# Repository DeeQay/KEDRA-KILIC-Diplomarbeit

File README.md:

<div align="center">

# LiDAR Mapping RC Vehicle

**Remote-controlled vehicle with real-time 360° LiDAR mapping and on-controller path planning**

Diploma thesis (Diplomarbeit) · HTL Donaustadt, Vienna · 2023/24
**David Kedra** and **Berdan Kilic**

</div>

## Overview

A four-wheel vehicle carries a 360° laser distance sensor (LiDAR) and streams its measurements over Bluetooth to a handheld controller. The controller turns the raw data into a live top-down map of the vehicle's surroundings, shows it on a 3.5" display and drives the vehicle via joystick. The user can pick any point on the map, and the controller computes and draws the shortest route around the obstacles to get there.

Both devices run on ESP32 microcontrollers. The firmware, the communication protocol and the controller PCB were designed from scratch.

<table>
  <tr>
    <td align="center"><br><sub>The real environment</sub></td>
    <td align="center"><br><sub>The same corner as seen on the controller</sub></td>
  </tr>
</table>

## The problem

A remote-controlled vehicle is only really usable while the operator can see it. Once it drives around a corner or into another room, the operator has no idea what is around it. That rules out exactly the use cases where such a vehicle would be most helpful, such as inspection, surveillance or exploring spaces a person cannot easily enter. A camera stream is the usual answer, but it needs a lot of bandwidth and only shows one direction.

**Goal of the thesis:** give the operator a full 360° picture of the vehicle's surroundings in real time, over a simple low-bandwidth wireless link, and help them find a route to a chosen point.

## The solution

| Challenge | Approach |
|---|---|
| See all directions at once | LD19 360° LiDAR on the vehicle, read over UART at 230 400 baud, every packet verified with CRC-8 |
| Send scan data over a slow wireless link | Own lightweight message protocol over Bluetooth Classic (SPP). Only *angle + distance* pairs are sent, paced by a hardware timer interrupt |
| Sensor noise | Plausibility filter on the controller that discards physically impossible jumps between consecutive measurements |
| Turn measurements into a map | Polar to Cartesian conversion into a 30 × 20 occupancy grid (free / obstacle / unknown), with ray-tracing to mark the free space between sensor and obstacle |
| Show it fast on a small display | Incremental rendering: only grid cells that changed since the last frame are redrawn on the 480 × 320 SPI display |
| Find a way to a target | Target selected with the joystick, shortest path computed with the **Lee algorithm** (breadth-first wavefront search, 8-neighbourhood) and drawn on the map |
| Drive the vehicle | Joystick values travel back over the same link and are mapped to PWM for four DC motors via two L298 H-bridges |

## System architecture

```mermaid
flowchart TB
    subgraph Vehicle["Vehicle · ESP32"]
        direction LR
        L[LD19 LiDAR<br/>360°, UART] --> P[Packet parser<br/>+ CRC-8]
        P --> T[Timer interrupt<br/>send scheduling]
        M[Motor control<br/>2× L298, 4 DC motors]
    end

    subgraph Controller["Controller · ESP32"]
        direction LR
        F[Noise filter] --> MAP[Occupancy grid<br/>30 × 20]
        MAP --> D[TFT display<br/>480 × 320, SPI]
        MAP --> LEE[Lee algorithm<br/>path planning]
        LEE --> D
        J[Joystick + button]
    end

    T -- "angle, distance" --> F
    J -- "x, y" --> M
```

Both arrows between the devices run over a single Bluetooth Classic connection (controller = master, vehicle = slave).

## Engineering decisions

**Choosing the platform.** The hardware went through three iterations before it worked reliably:

| Iteration | Setup | Why it was dropped |
|---|---|---|
| 1 | 2× Arduino Nano + HC-05 Bluetooth modules | Not enough memory and CPU for the map, display and LiDAR processing |
| 2 | Raspberry Pi 4 (controller) + ESP32 (vehicle) | No Linux driver library for the ILI9488 display. Writing one would have taken too long |
| 3 | 2× ESP32 with built-in Bluetooth | **Final.** Dropping the external modules also gave faster transfer, quicker pairing and lower latency |

**Optimising the mapping code.** The controller has to process LiDAR data, redraw the display and send joystick values at the same time, so the coordinate conversion was profiled on the ESP32. A benchmark of 720 rays took about 2200 ms. Caching sine and cosine per angle and pre-computing all constant scale factors brought it down to about 1500 ms, roughly **32 % faster**, see [`LidarMapper::calcPosition`](Programmcode/Fernsteuerung/LidarMapper.cpp).

**Low cost.** The main components (ESP32s, LiDAR, display, chassis with motors, motor drivers) cost about 130 €.

## Features

**Live 360° map** with the vehicle always in the centre. Five mapping modes, switched with the button:

| Mode | Behaviour |
|---|---|
| Save | Accumulates all measurements. Best while the vehicle stands still |
| Overwrite | New measurements replace old ones along the same ray. Best while driving |
| Full rotation | Redraws the map after each complete 360° sweep |
| Full rotation, slow | Same, with finer angular resolution |
| Automatic | Switches between *Save* and *Overwrite* depending on whether the joystick is idle |

**Route planning.** Press the joystick, move the cursor to a target, confirm. The shortest path around all known obstacles is calculated and shown:

<table>
  <tr>
    <td align="center"><br><sub>1. Select a target (blue)</sub></td>
    <td align="center"><br><sub>2. Shortest route around the wall (purple)</sub></td>
  </tr>
</table>

<details>
<summary><b>How the Lee algorithm works</b></summary>
<br>

Starting at the vehicle (`ST`), every reachable cell is labelled with its distance in steps, wave by wave, until the target (`EN`) is reached. Obstacles (`##`) are never entered. Walking back from the target along decreasing numbers gives the shortest path.

Implementation: [`LeeAlgorithm.cpp`](Programmcode/Fernsteuerung/LeeAlgorithm.cpp)
</details>

**More:**
- Adjustable range from 0.5 m to 12 m in 0.5 m steps (hold the joystick)
- Reset the map (hold the button)
- Automatic Bluetooth reconnect when the link drops

## Hardware

<table>
  <tr>
    <td align="center"><br><sub>Vehicle with LD19 LiDAR on top</sub></td>
    <td align="center"><br><sub>Controller on its own PCB</sub></td>
  </tr>
</table>

| | Vehicle | Controller |
|---|---|---|
| Microcontroller | ESP32 | ESP32 DevKit V1 |
| Input | LDROBOT LD19 360° LiDAR | Analog joystick (SparkFun COM-09032), push button |
| Output | 4 DC motors via 2× L298 H-bridge | 3.5" TFT, 480 × 320, ILI9488, SPI |
| Design files | [`Platinen/Fahrzeug`](Platinen/Fahrzeug) | [`Platinen/Fernsteuerung`](Platinen/Fernsteuerung) |

<details>
<summary><b>Controller schematic</b></summary>
<br>

</details>

## Bluetooth protocol

Each message is a short list of integers, sent as ASCII digits:

```
<type> \n <value 1> \n <value 2> \0
```

| Type | Direction | Values |
|---|---|---|
| `0` JOYSTICK | controller → vehicle | x, y (12-bit ADC) |
| `1` LIDAR | vehicle → controller | angle (°), distance (mm) |

The receiver checks length and characters and drops corrupted messages instead of acting on them.

## Repository structure

```
Programmcode/
├── Fahrzeug/           Vehicle firmware: LiDAR driver, motor control, Bluetooth slave
└── Fernsteuerung/      Controller firmware: mapping, display, Lee algorithm, joystick, Bluetooth master
Platinen/               EAGLE schematics (.sch) and board layouts (.brd)
docs/                   Presentation, project pitch, images
Lidar doku/             LD19 datasheet
Display doku/           Display manual, Adafruit GFX reference
Umgebungsspeicherung/   Early test code for the mapping logic
```

## Build and flash

1. Install the [Arduino IDE](https://www.arduino.cc/en/software) and the **esp32** board package by Espressif.
2. Install the controller libraries via the Library Manager: `Adafruit GFX Library`, `ILI9486_SPI`.
3. Upload `Programmcode/Fahrzeug/Fahrzeug.ino` to the vehicle ESP32.
4. Upload `Programmcode/Fernsteuerung/Fernsteuerung.ino` to the controller ESP32.
5. Power both. The controller finds and connects to the vehicle automatically.

> On the vehicle the LiDAR is read on the same hardware UART as the USB serial port, so its TX line may need to be disconnected while uploading.

## Team

| | Responsibilities |
|---|---|
| **David Kedra** ([@DeeQay](https://github.com/DeeQay)), project lead | Bluetooth communication and protocol, map visualisation, environment mapping, route planning. Controller hardware and PCB |
| **Berdan Kilic** ([@kilic7](https://github.com/kilic7)) | Vehicle control and motor drivers, 360° LiDAR data acquisition. Vehicle hardware and PCB |

Supervisors: Ahmet Kilic, Heinrich Haager

## Documents

- [**Diploma thesis** (PDF, German)](docs/Diplomarbeit.pdf)
- [Final presentation (PDF, German)](docs/Diplomarbeit_Praesentation.pdf)
- [Project pitch, October 2023 (PDF, German)](docs/Projektvorstellung_2023-10.pdf)
- [Project description (German)](Diplomarbeit%20Projektbeschreibung.docx)

## Limitations and next steps

- **No odometry.** The map is always relative to the vehicle's current position and is refreshed while driving, not stitched into one global map. Wheel encoders or an IMU would allow real SLAM.
- **Route is advisory.** The path is shown to the operator, the vehicle does not follow it on its own yet.
- **Bandwidth.** Bluetooth Classic limits how many points per second reach the controller, which is why the grid is kept coarse (30 × 20). BLE or Wi-Fi (ESP-NOW) would allow a finer map.

---

<sub>Code comments and project documents are in German.</sub>

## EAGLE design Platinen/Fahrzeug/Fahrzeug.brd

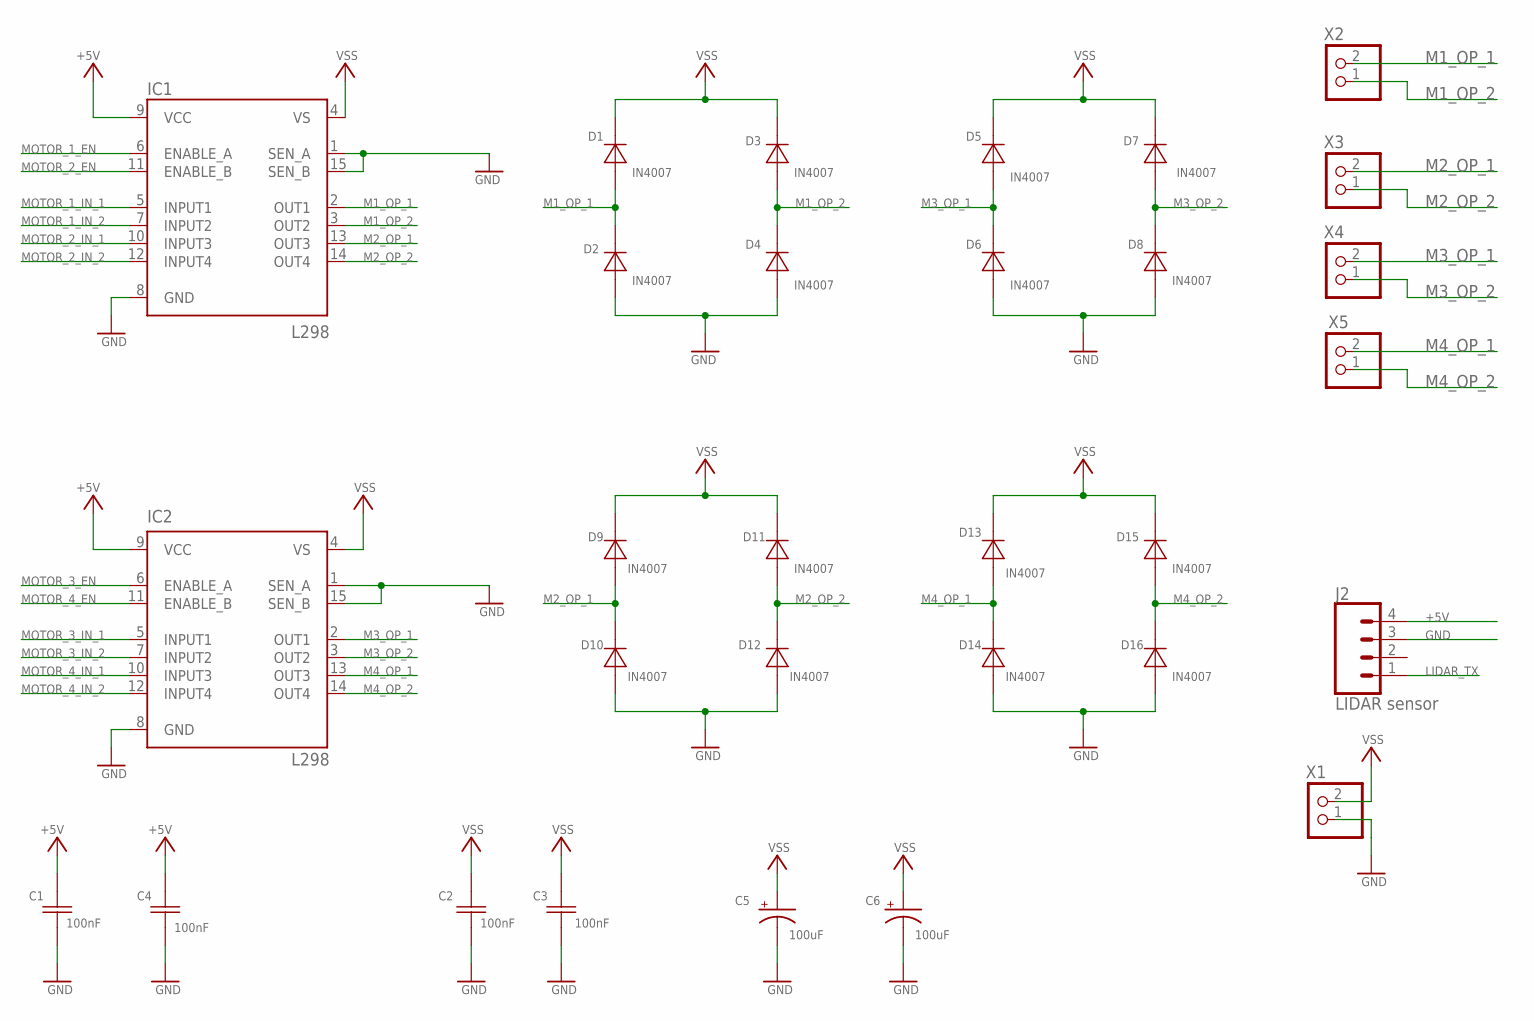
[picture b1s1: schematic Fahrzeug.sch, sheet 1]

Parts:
C1, C2, C3, C4: 100nF; R1206
C5, C6: 100uF; CPOL-RADIAL-2.5MM-6.5MM
D1, D2, D3, D4, D5, D6, D7, D8, D9, D10, D11, D12, D13, D14, D15, D16: IN4007; DO214AC
IC1, IC2: L298; MULTIWATT-15
J2: LIDAR sensor; MOLEX-1X4
X1, X2, X3, X4, X5: PINHD-1X2; 1X02

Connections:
+5V: C1.2, C4.2, IC1.9 (VCC), IC2.9 (VCC), J2.4; also elsewhere on the board
GND: C1.1, C2.1, C3.1, C4.1, C5.2 (-), C6.2 (-), D2.A, D4.A, D6.A, D8.A, D10.A, D12.A, D14.A, D16.A, IC1.1 (SEN_A), IC1.8 (GND), IC1.15 (SEN_B), IC2.1 (SEN_A), IC2.8 (GND), IC2.15 (SEN_B), J2.3, X1.1; also elsewhere on the board
LIDAR_TX: J2.1; also elsewhere on the board
M1_OP_1: D1.A, D2.C, IC1.2 (OUT1), X2.2
M1_OP_2: D3.A, D4.C, IC1.3 (OUT2), X2.1
M2_OP_1: D9.A, D10.C, IC1.13 (OUT3), X3.2
M2_OP_2: D11.A, D12.C, IC1.14 (OUT4), X3.1
M3_OP_1: D5.A, D6.C, IC2.2 (OUT1), X4.2
M3_OP_2: D7.A, D8.C, IC2.3 (OUT2), X4.1
M4_OP_1: D13.A, D14.C, IC2.13 (OUT3), X5.2
M4_OP_2: D15.A, D16.C, IC2.14 (OUT4), X5.1
MOTOR_1_EN: IC1.6 (ENABLE_A); also elsewhere on the board
MOTOR_1_IN_1: IC1.5 (INPUT1); also elsewhere on the board
MOTOR_1_IN_2: IC1.7 (INPUT2); also elsewhere on the board
MOTOR_2_EN: IC1.11 (ENABLE_B); also elsewhere on the board
MOTOR_2_IN_1: IC1.10 (INPUT3); also elsewhere on the board
MOTOR_2_IN_2: IC1.12 (INPUT4); also elsewhere on the board
MOTOR_3_EN: IC2.6 (ENABLE_A); also elsewhere on the board
MOTOR_3_IN_1: IC2.5 (INPUT1); also elsewhere on the board
MOTOR_3_IN_2: IC2.7 (INPUT2); also elsewhere on the board
MOTOR_4_EN: IC2.11 (ENABLE_B); also elsewhere on the board
MOTOR_4_IN_1: IC2.10 (INPUT3); also elsewhere on the board
MOTOR_4_IN_2: IC2.12 (INPUT4); also elsewhere on the board
VSS: C2.2, C3.2, C5.1 (+), C6.1 (+), D1.C, D3.C, D5.C, D7.C, D9.C, D11.C, D13.C, D15.C, IC1.4 (VS), IC2.4 (VS), X1.2; also elsewhere on the board

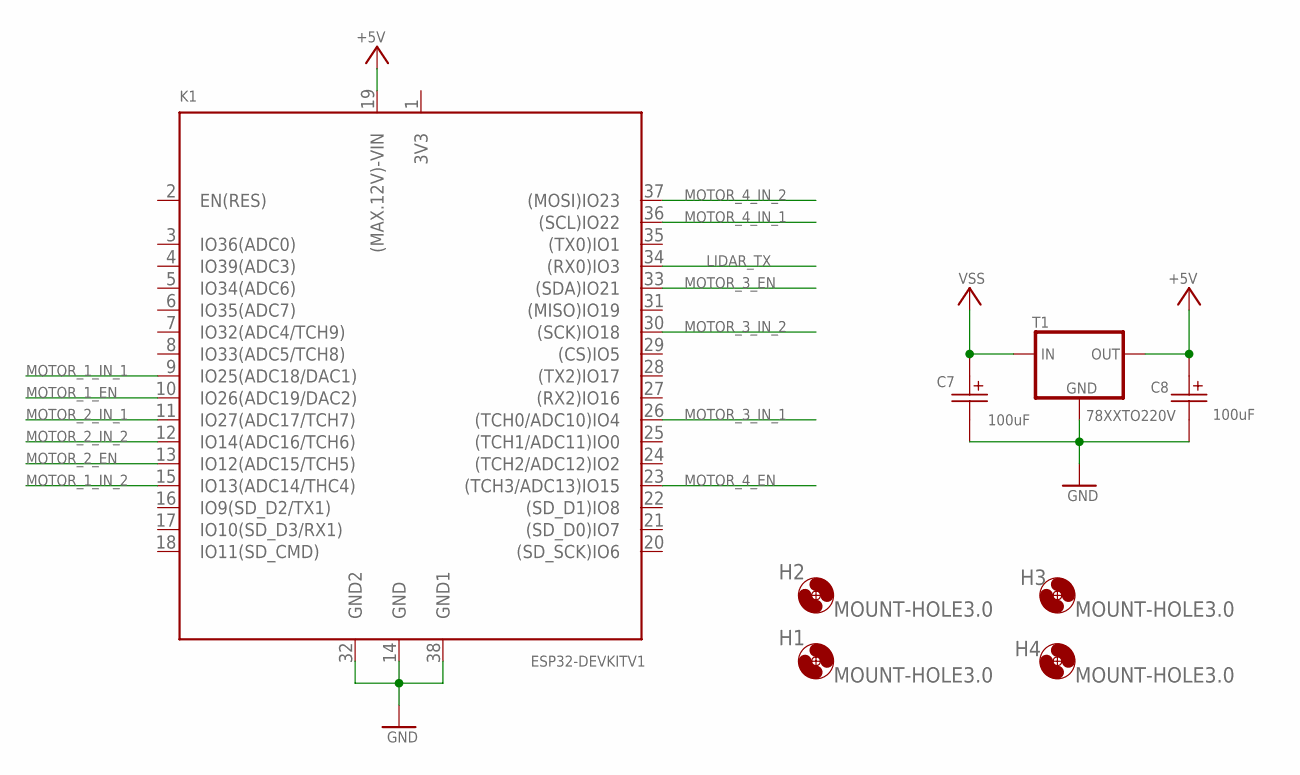
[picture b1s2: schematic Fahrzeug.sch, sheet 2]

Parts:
C7, C8: 100uF; E2,5-5
H1, H2, H3, H4: MOUNT-HOLE3.0; 3,0
K1: ESP32DEVKITV11000MIL; ESP32-DEVKITV1
T1: 78XXTO220V; 78-TO220V

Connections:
+5V: C8.+, K1.19 ((MAX.12V)-VIN), T1.OUT; also elsewhere on the board
GND: C7.-, C8.-, K1.14 (GND), K1.32 (GND2), K1.38 (GND1), T1.GND; also elsewhere on the board
LIDAR_TX: K1.34 ((RX0)IO3); also elsewhere on the board
MOTOR_1_EN: K1.10 (IO26(ADC19/DAC2)); also elsewhere on the board
MOTOR_1_IN_1: K1.9 (IO25(ADC18/DAC1)); also elsewhere on the board
MOTOR_1_IN_2: K1.15 (IO13(ADC14/THC4)); also elsewhere on the board
MOTOR_2_EN: K1.13 (IO12(ADC15/TCH5)); also elsewhere on the board
MOTOR_2_IN_1: K1.11 (IO27(ADC17/TCH7)); also elsewhere on the board
MOTOR_2_IN_2: K1.12 (IO14(ADC16/TCH6)); also elsewhere on the board
MOTOR_3_EN: K1.33 ((SDA)IO21); also elsewhere on the board
MOTOR_3_IN_1: K1.26 ((TCH0/ADC10)IO4); also elsewhere on the board
MOTOR_3_IN_2: K1.30 ((SCK)IO18); also elsewhere on the board
MOTOR_4_EN: K1.23 ((TCH3/ADC13)IO15); also elsewhere on the board
MOTOR_4_IN_1: K1.36 ((SCL)IO22); also elsewhere on the board
MOTOR_4_IN_2: K1.37 ((MOSI)IO23); also elsewhere on the board
VSS: C7.+, T1.IN; also elsewhere on the board

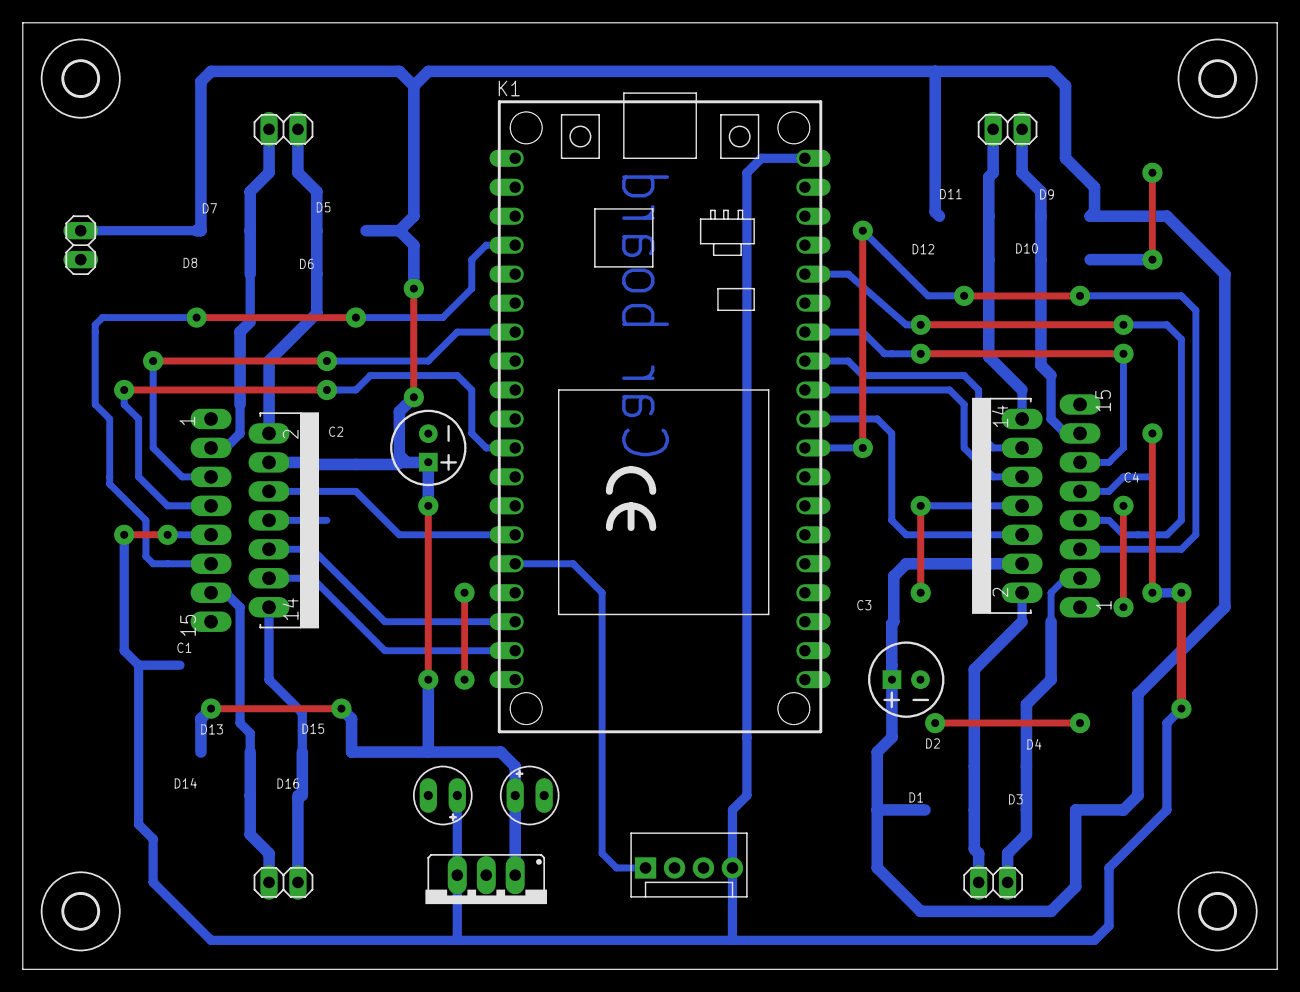
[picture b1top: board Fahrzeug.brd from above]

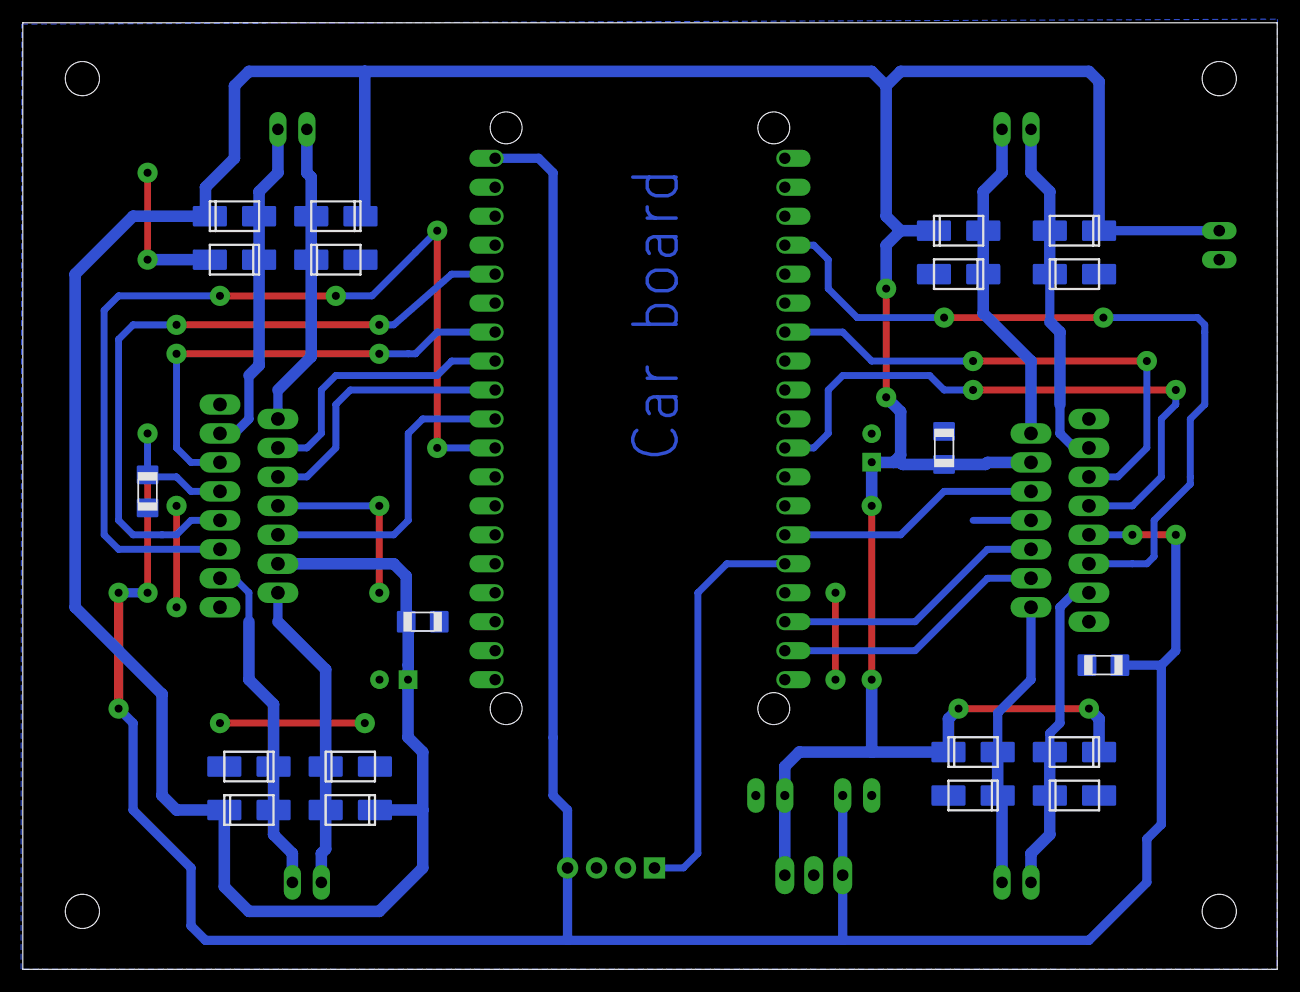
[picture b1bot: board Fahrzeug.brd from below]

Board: 2 copper layers, 110.0 x 83.0 mm, 43 parts (20 on the bottom side), 24 nets.

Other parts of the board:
DRILEGEND: DRILEGEND
U$3, U$4: ARROW-->
U$5, U$6: ARROW<--

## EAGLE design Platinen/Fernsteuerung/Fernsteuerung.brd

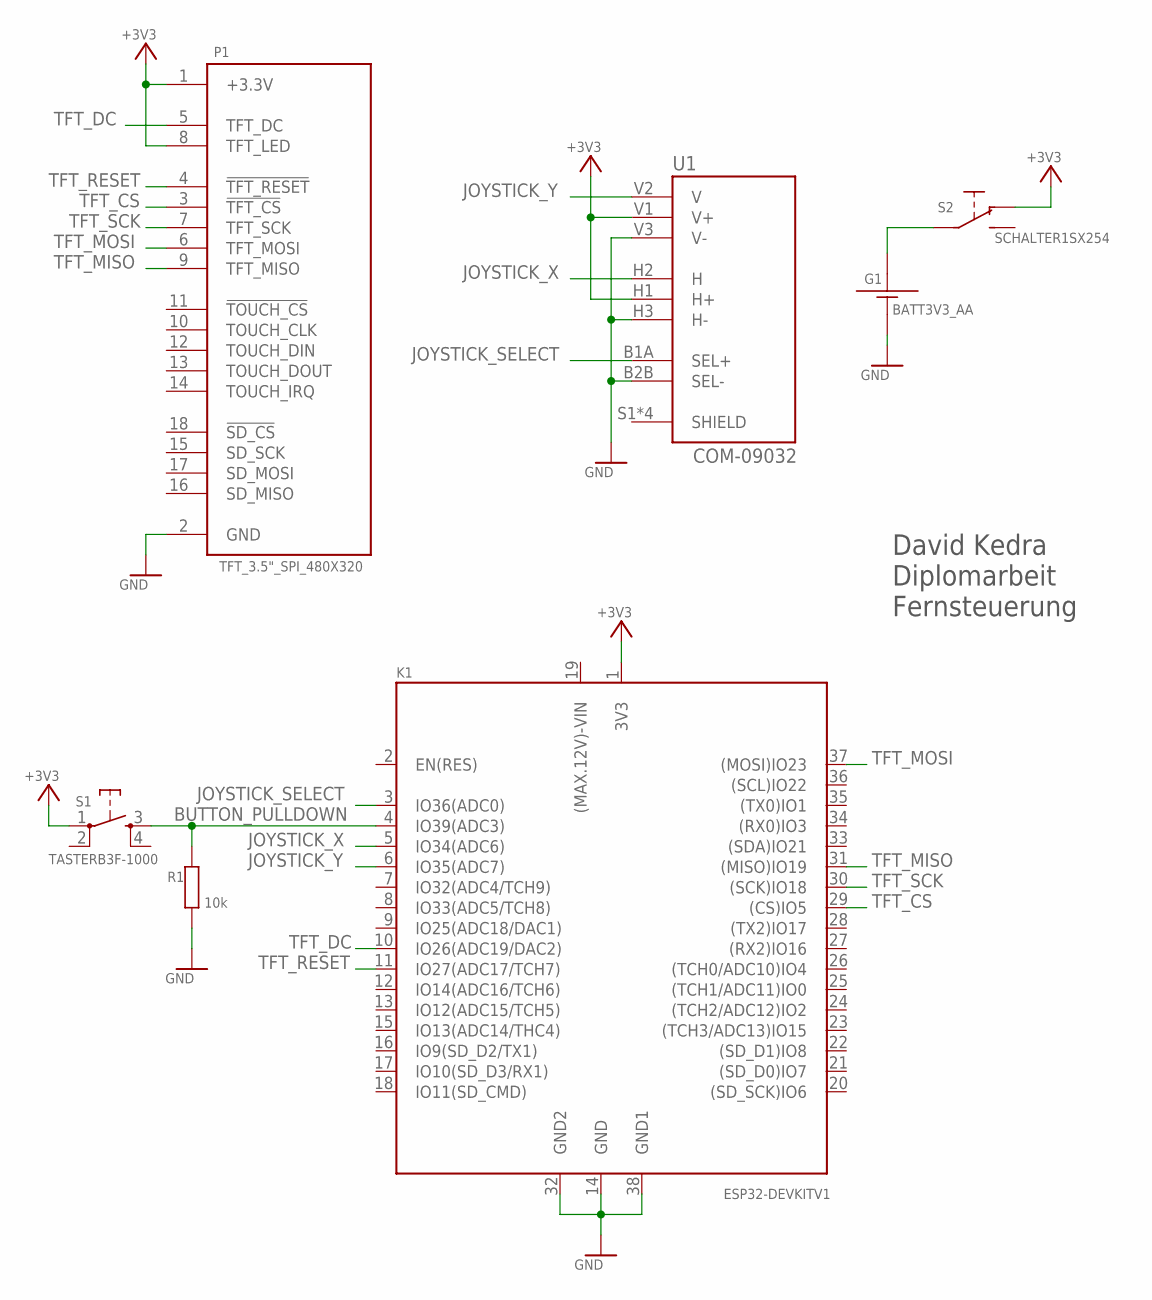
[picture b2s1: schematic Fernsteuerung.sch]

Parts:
G1: BATT3V3_AA; BATT-3V3-AA
K1: ESP32DEVKITV11000MIL; ESP32-DEVKITV1
P1: TFT_3.5"_SPI_480X320
R1: 10k; R1206
S1: TASTERB3F-1000; B3F-10XX
S2: SCHALTER1SX254; SX254
U1: COM-09032; XDCR_COM-09032

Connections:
+3V3: K1.1 (3V3), P1.1 (+3.3V), P1.8 (TFT_LED), S1.1, S2.O1, U1.H1 (H+), U1.V1 (V+)
BATTERY_+3V3: G1.PLUS, S2.W1
BUTTON_PULLDOWN: K1.4 (IO39(ADC3)), R1.2, S1.3 (S)
GND: G1.MINUS, K1.14 (GND), K1.32 (GND2), K1.38 (GND1), P1.2 (GND), R1.1, U1.B2B (SEL-), U1.H3 (H-), U1.V3 (V-)
JOYSTICK_SELECT: K1.3 (IO36(ADC0)), U1.B1A (SEL+)
JOYSTICK_X: K1.5 (IO34(ADC6)), U1.H2 (H)
JOYSTICK_Y: K1.6 (IO35(ADC7)), U1.V2 (V)
TFT_CS: K1.29 ((CS)IO5), P1.3 (!TFT_CS!)
TFT_DC: K1.10 (IO26(ADC19/DAC2)), P1.5 (TFT_DC)
TFT_MISO: K1.31 ((MISO)IO19), P1.9 (TFT_MISO)
TFT_MOSI: K1.37 ((MOSI)IO23), P1.6 (TFT_MOSI)
TFT_RESET: K1.11 (IO27(ADC17/TCH7)), P1.4 (!TFT_RESET!)
TFT_SCK: K1.30 ((SCK)IO18), P1.7 (TFT_SCK)

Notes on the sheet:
David Kedra Diplomarbeit Fernsteuerung

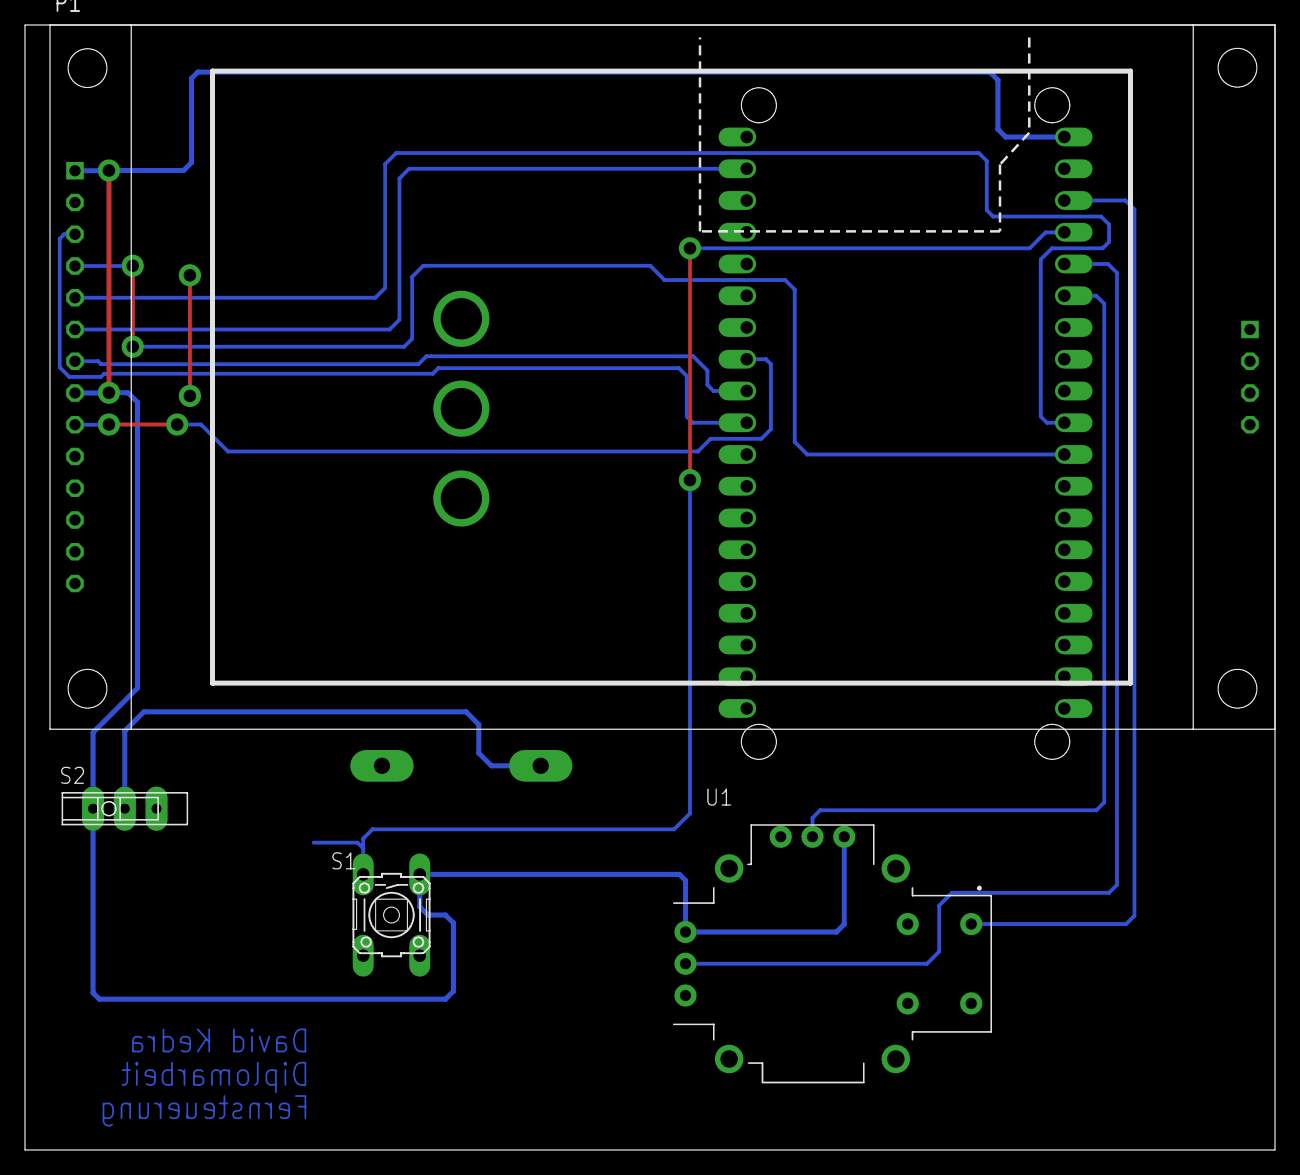
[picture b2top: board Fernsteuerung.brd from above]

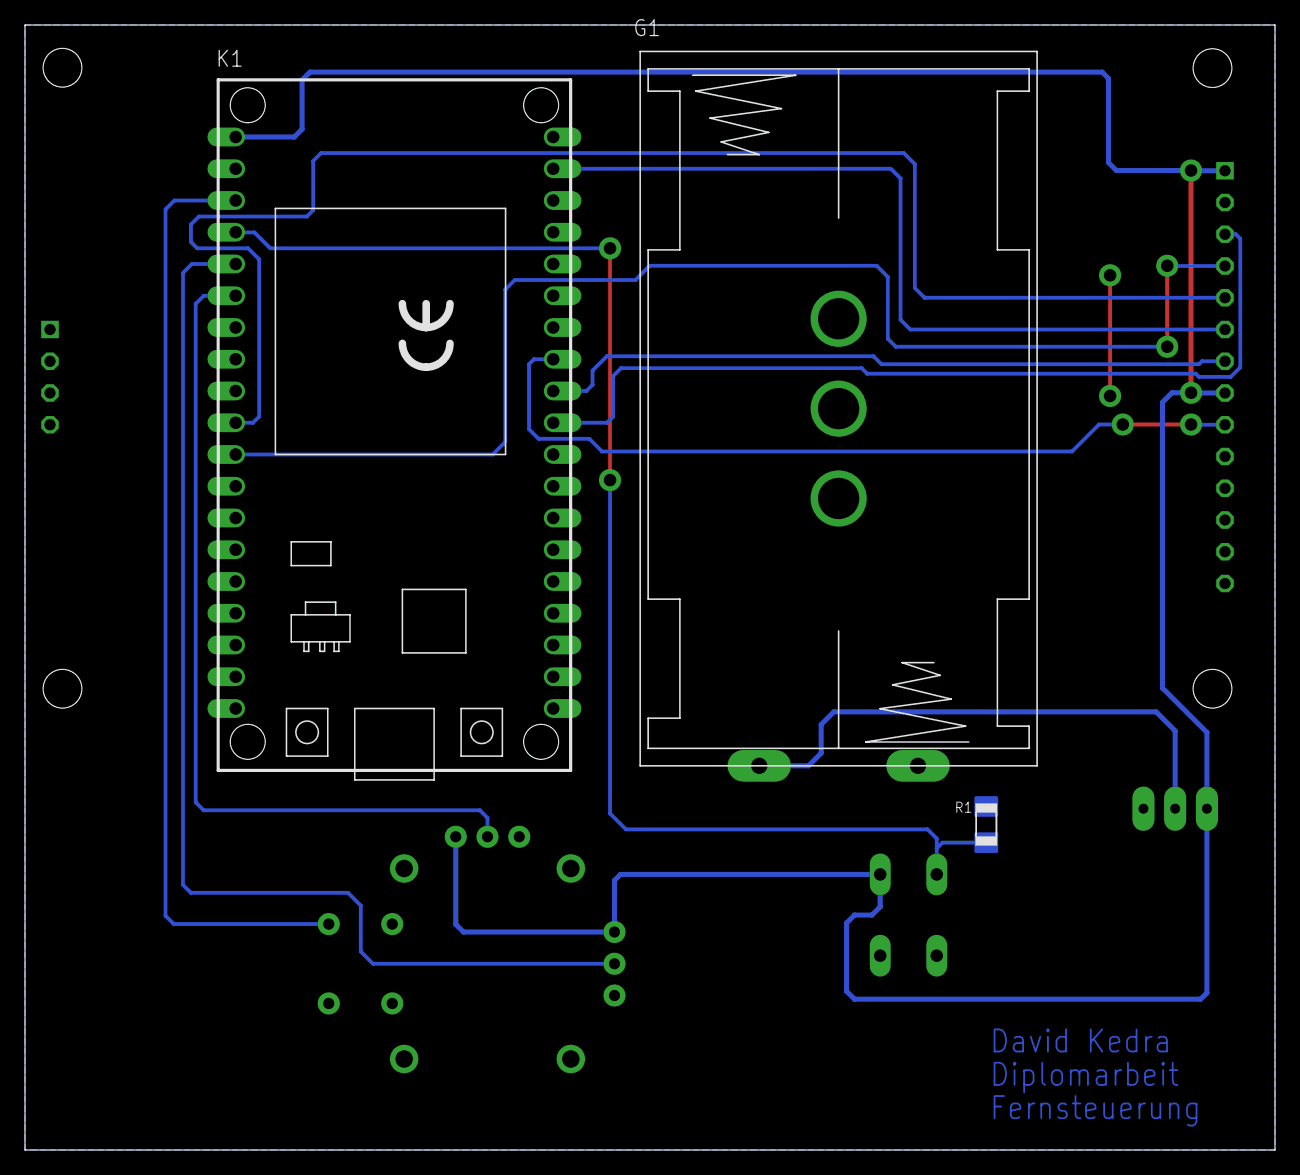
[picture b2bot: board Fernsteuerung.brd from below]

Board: 2 copper layers, 100.0 x 90.0 mm, 12 parts (3 on the bottom side), 13 nets.

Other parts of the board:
DRILEGEND: DRILEGEND
U$1, U$2: ARROW-->
U$3, U$4: ARROW<--

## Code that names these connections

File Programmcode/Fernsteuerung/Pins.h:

// Programmersteller: David KEDRA

class Pin {
public:
  // Display
  static const int TFT_CS = 5;  // fix für VSPI
  static const int TFT_DC = 26;
  static const int TFT_RST = 27;
  // VSPI:
  // MOSI -> 23
  // MISO -> 19
  // SCK/CLK -> 18

  // Joystick
  static const int JOYSTICK_X = 35;
  static const int JOYSTICK_Y = 34;
  static const int JOYSTICK_SELECT = 36;

  // Button
  static const int BUTTON = 39;
};

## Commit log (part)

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2023-09-09 Bluetooth Kommunikation Senden und Empfangen
    Erster upload der Klasse Bluetooth Kommunikation für zwei Arduino Geräte.
    Datum der Programmierung: 23-24.8.2023
2023-09-09 Arduino display
    test code für Arduino Display ili9488 driver
    Programming Datum: 2.9.2023
2023-09-11 SendMessage type change & connection status (nicht fertig)
    Bluetooth Nachrichtentyp geändert von string zu int.
    Beginn von Ping (nicht fertig): Überprüfung ob die Bluetooth Geräte miteinander verbunden sind.
2023-09-15 Ordnernamen ändern
2023-09-15 fahrzeug steuerung
2023-09-15 bessere Bluetooth Kommunikation
    TX/RX Pins geändert von 1/2 zu 3/4.
    bessere Bluetooth Kommunikation
2023-09-22 Bluetooth Klasse fertig
    baudrate erhöht auf 38400.
    Es wird jetzt ein character array gesendet.
    Controller und Fahrzeug code getrennt. Beide können Senden und Empfangen.
2023-09-29 Lidar start
    Lidar Pins und Datenblatt hinzugefügt
2023-09-29 Pin änderung + Kommentare hinzugefügt
    TX und RX Pins vertauscht.
    Kommentare und Konsolenausgaben in Deutsch.
    Mehrere Kommentare hinzugefügt.
2023-09-29 Eagle Stromlaufplan
    Bluetooth test Stromlaufplan hinzugefügt.
2023-11-18 bluetooth angepasst auf esp32.
    bluetooth angepasst auf esp32.
    baudrate auf 115200 geändert.
    controller und auto code.
    getestet mit arduino und esp32. Funktioniert.
2023-11-18 unnötiges löschen
2024-01-12 Car bluetooth + joystick update
2024-01-12 Controller bluetooth und joystick update
    Zusammen aktualisiert mit "Car bluetooth und joystick update"
2024-01-12 Kommentar hinzufügen
2024-01-13 Umgebungsspeicherung
    Geschrieben am 12.1 und 13.1.2024.
    Umgebung wird in einem 2D Vektor (wie ein 2D Array) gespeichert: `position`.
    Winkel `angle` und Entfernung `distance` wird verarbeitet zu x und y Koordinaten und im Array gespeichert.
    Die Auflösung des Speichers kann eingestellt werden.
2024-02-23 update bluetooth für zwei ESP32
    Zwei ESP32 mit buildin Bluetooth: ohne HC05.
    Verbindung funktioniert. Einbindung in bluetooth Klasse muss gemacht werden.
2024-03-08 update display code für esp32
2024-03-08 Bluetooth Verbindung 2x ESP32
    Änderung des Codes und Testung von Senden und Empangen von Daten zwischen zwei ESP32's.
    Testung erfolgreich.
    Problem: Delay erforderlich, da es sonst zu falschen Dateiübertragung kommt.
    Lösungsansatz/todo: Überprüfung der empfangenen Daten, in dem man zu jedem Paket zusätzliche Überprüfungs-Bits verschickt.
2024-03-15 Umgebungsspeicherung und dessen Anzeige auf ESP32
    Umgebungsspeicherung und dessen Anzeige erfolgreich auf ESP32 mit TFT-Display funktioniert.
2024-03-15 Umgebungsspeicherung und dessen Anzeige INFO!
    ACHTUNG: C:\Users\Lenovo\Documents\Arduino\libraries\ILI9486_SPI\src
    FILE: ILI9486_SPI.cpp
    Ändern #define SPI_SPEED auf 40MHz
2024-03-16 Update Bluetooth.cpp for Controller
2024-03-16 Update Bluetooth.cpp für Car
2024-03-17 Umgebungsspeicherung um einiges optimiert.
    ganzen Tag gearbeitet um den code schneller zu machen.
    Notiz: Dieser Part
    ```Cpp
    pos.x = (xFloat * halfMaxPosX + 0.5) * MAX_POSITION_X;
    pos.y = (yFloat * halfMaxPosY + 0.5) * MAX_POSITION_Y;
    ```
2024-03-17 Dokumentation für die Optimierung der Umgebungsspeicherung erstellt
2024-03-21 Eagle Fernsteuerung + Display library
    Eagle library für das TFT SPI 3.5inch 480x320 Display mit dem Treiber ILI9488 erstellt.
    Schematic für die Fernsteuerung angefangen.
2024-03-22 Freitag commit
2024-03-23 Code anpassen für Empfangen/Senden der Werte für Lidar
2024-03-25 LidarMapper für die Umgebungsspeicherung fixen
    Hatte einen ERROR!
    Wurde gelöst und funktioniert wieder.
    TODO: Testzeit für die Dokumentation neu messen
2024-03-29 Aktuelle Codeversion
    Sensor integriert
2024-03-29 Nur FORMATIERUNG!
    keine Änderung im Code. Nur auto-formatierung.
2024-03-29 LidarMapper/TFT/pins Klassen + Object Lücken füllen
    Klassen für TFT und Pins erstellt.
    angle von float zu int geändert.
    TFT: Bei einer Lücke zwischen zwei OBJECT werden gefüllt mit einer Linie.
2024-03-31 `distance, angle` -> `angle, distance`
    Umgebungsspeicherung Parameter Reihenfolge anpassen, sodass es so wie im der Rest des Codes ist.
2024-03-31 Kommentare
2024-04-02 BT: Format und Text Änderungen
    Keine Änderung in der Logik
2024-04-05 Umgebungsumgebung code funktioniert nicht!
2024-04-18 Umstrukturierung (KEIN Code geändert)
2024-04-18 Eagle Fernsteuerung
2024-04-19 board fersteuerung
2024-04-19 Fernsteuerung Plaine fertig
2024-04-20 Fernsteuerung Board fertig
2024-04-20 Ordner "Bluetooth" ändern auf "Programmcode"
    code wurde nicht geändert
2024-04-20 Umgebung und Bildschirm zusammengefügt mit dem Rest des Codes
2024-04-20 keine Code Änderung
2024-04-22 lee-alg base
2024-04-22 Platine
    platine auf github
2024-04-22 unnötig
2024-04-22 LeeAlgorithmus base in Code hinzufügen (Funktioniert noch nicht zusammen))
2024-04-22 Lee-Alg. kommentieren
2024-05-19 lidar sensor auf bildschirm
2024-05-19 Selection (bluetooth in loop auskommentiert)
2024-05-20 Display info + Routenfindung + Bluetooth connect fix + better UX & features
2024-05-21 fix 15 12 meter + fix wrong values
2024-05-21 besserer Überschreiben Modus
2024-05-21 Bluetooth fix + Neuer Modus "Automatisch" + verbesserter Modus "Volle Umdrehung"
2024-05-23 NEIN
2024-05-23 joystick werte ändern beim fahrzeug
2024-05-23 ende

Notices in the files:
parts and their libraries:
SparkFun-Capacitors: Licensing: Creative Commons ShareAlike 4.0 International - https://creativecommons.org/licenses/by-sa/4.0
